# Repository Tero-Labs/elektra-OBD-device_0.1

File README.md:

> Designing Electric Vehicles capable of autonomously participating in a decentralized, sharing economy at a much lower cost than now.   

:warning: :warning: :warning:
>Deprecation Warning: 
This repo is no longer maintained. Please have a look at the newer [elektra-OBD-Device_v1.0](https://github.com/Tero-Labs/elektra-OBD-device_v1.0) based on the ESP32.

# Elektra-OBD-Device_v0.1
OBD data monitoring tool based on MCP2551 & MCP2515 for project elektra. The device is designed as a Raspberry Pi hat compatible with Raspberry Pi Zero W.

## Board 
Top             |  Bottom
:-------------------------:|:-------------------------:
  |  

Eagle project files  are given. The Cam output files are also present for ordering through PCB fabrication services.

## Assembly & Enclosure

Board             |  Enclosure
:-------------------------:|:-------------------------:
  |  

## Enclosure Printing Instructions
+ 0.3 layer height
+ PLA/ABS (ABS preferred)
+ 4x m1.5 countersink screws required

# License
<br />This work is licensed under a <a rel="license" href="http://creativecommons.org/licenses/by-nc-sa/4.0/">Creative Commons Attribution-NonCommercial-ShareAlike 4.0 International License</a>.

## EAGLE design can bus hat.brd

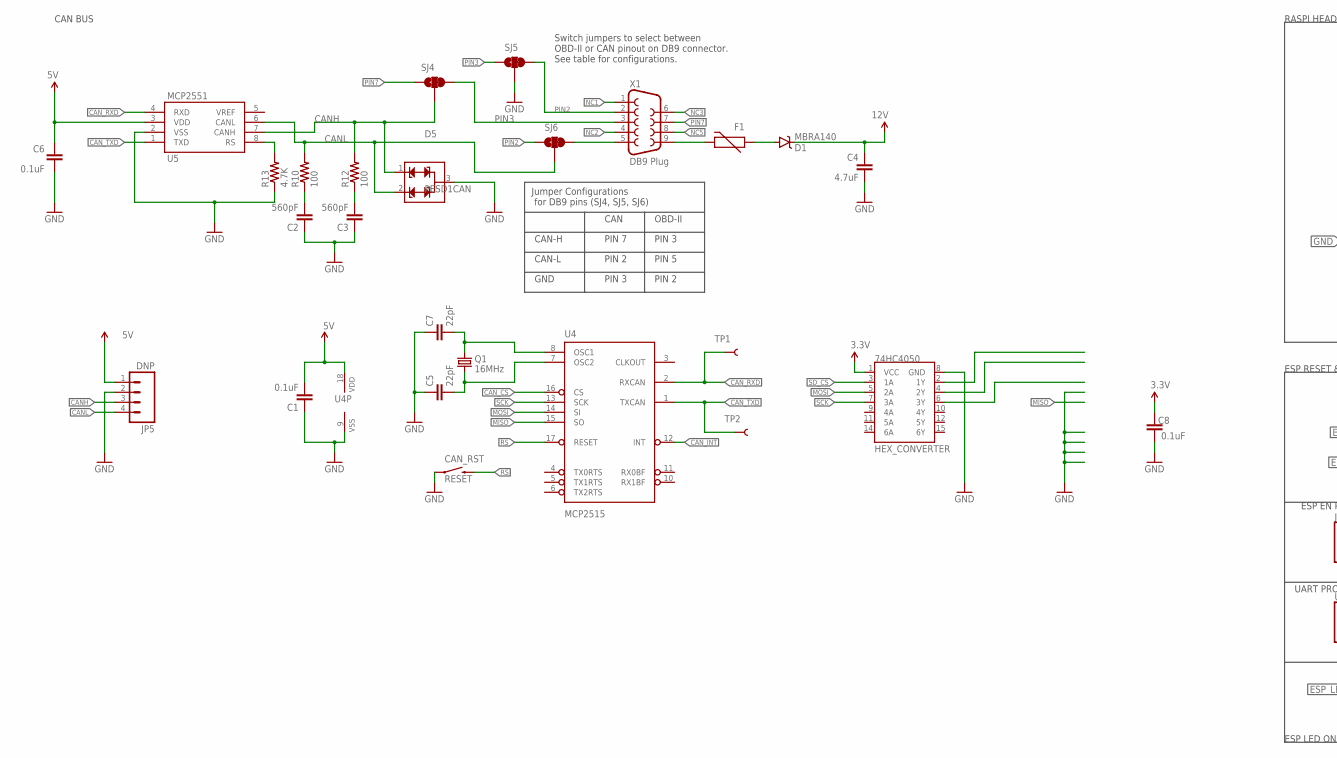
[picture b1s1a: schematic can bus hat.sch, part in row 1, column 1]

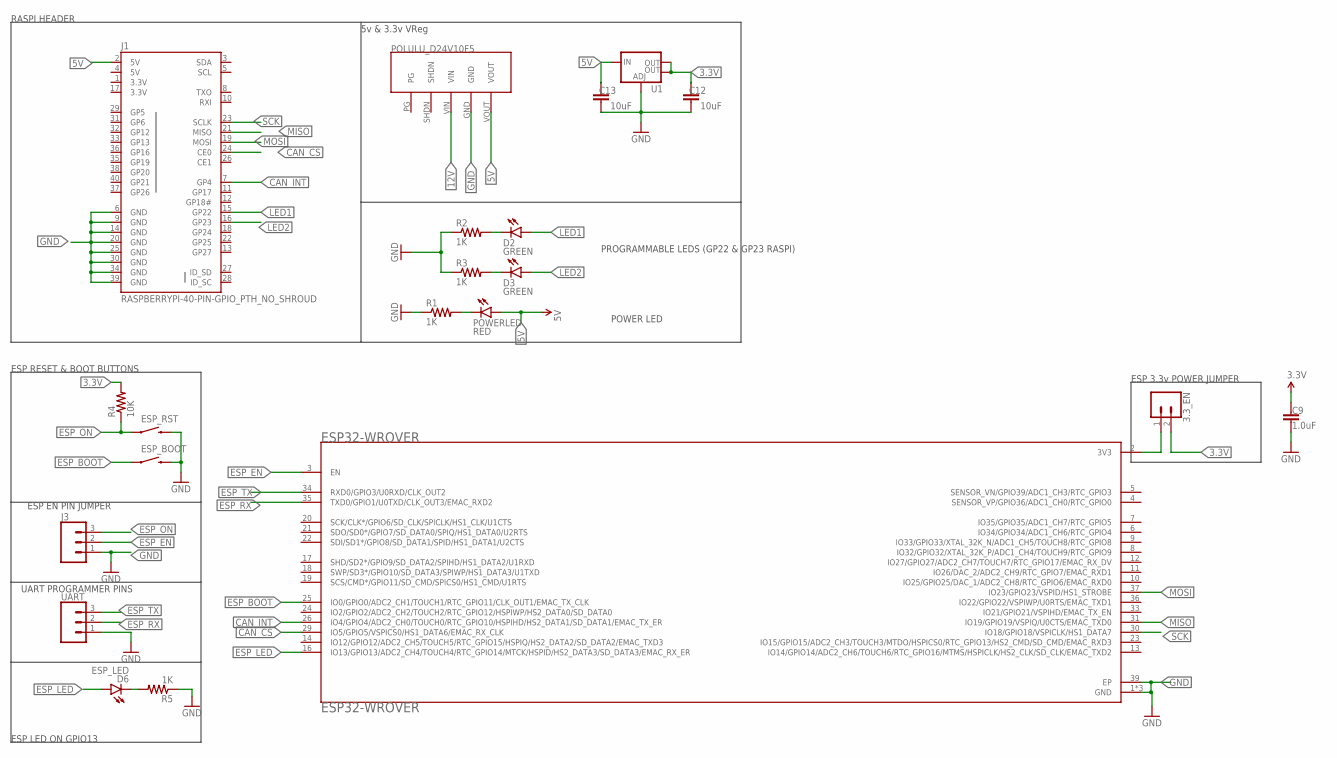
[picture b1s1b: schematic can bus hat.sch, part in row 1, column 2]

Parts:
3.3_EN: CONN_02; 1X02
74HC4050: HEX_CONVERTER; SO016
C1, C6, C8: 0.1uF; 0603-CAP
C2, C3: 560pF; 0603-CAP
C4: 4.7uF; 0603-CAP
C5, C7: 22pF; 0603-CAP
C9: 1.0uF; 0603-CAP
C12, C13: 10uF; 0603-CAP
CAN_RST: RESET; TACTILE-SWITCH-SMD
D1: MBRA140; SMA-DIODE
D2, D3: GREEN; LED-0603
D5: PESD1CAN; SOT23-3
D6: ESP_LED; LED-0603
ESP32-WROVER: ESP32-WROVER; XCVR_ESP32-WROVER
ESP_BOOT: RESET; TACTILE-SWITCH-SMD
ESP_RST: RESET; TACTILE-SWITCH-SMD
F1: PTCTHERMISTOR1206; PTC-1206
J1: RASPBERRYPI-40-PIN-GPIO_PTH_NO_SHROUD; 2X20
J3: CONN_03; 1X03
JP5: DNP; 1X04
POLULU_D24V10F5: POLOLU5V,1ASTEP-DOWNVOLTAGEREGULATORD24V10F5; POLULU-VREG
POWERLED: RED; LED-0603
Q1: 16MHz; CRYSTAL-SMD-5X3
R1, R2, R3, R5: 1K; 0603-RES
R4: 10K; 0603-RES
R10, R12: 100; 0603-RES
R13: 4.7K; 0603-RES
SJ4, SJ5, SJ6: JUMPER-PAD-3-2OF3_NC_BY_TRACE_SMALL; PAD-JUMPER-3-2OF3_NC_BY_TRACE_YES_SILK_FULL_BOX
TP1, TP2: TEST-POINT3X5; PAD.03X.05
U1: VR_REGULATOR_LM1117SOT223; SOT223
U4: MCP2515; SO-18W
U5: MCP2551; SO08
UART: CONN_03; 1X03
X1: DB9 Plug; DB9_MALE

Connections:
3.3V: 3.3_EN.2, 74HC4050.1 (VCC), C8.2, C9.1, C12.2, J1.1 (3.3V), J1.17 (3.3V), R4.2, U1.2 (OUT), U1.4 (OUT)
5V: C1.2, C6.2, C13.2, J1.2 (5V), J1.4 (5V), JP5.1, POLULU_D24V10F5.VOUT, POWERLED.A, U1.3 (IN), U4.18 (VDD), U5.3 (VDD)
12V: C4.1, D1.C, POLULU_D24V10F5.VIN
CANH: D5.1, JP5.3, R12.2, SJ4.2, U5.7 (CANH)
CANL: D5.2, JP5.4, R10.2, SJ6.2, U5.6 (CANL)
CAN_CS: ESP32-WROVER.29 (IO5/GPIO5/VSPICS0/HS1_DATA6/EMAC_RX_CLK), J1.24 (CE0), U4.16 (CS)
CAN_INT: ESP32-WROVER.26 (IO4/GPIO4/ADC2_CH0/TOUCH0/RTC_GPIO10/HS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), J1.7 (GP4), U4.12 (INT)
CAN_RXD: TP1.P$1, U4.2 (RXCAN), U5.4 (RXD)
CAN_TXD: TP2.P$1, U4.1 (TXCAN), U5.1 (TXD)
ESP_BOOT: ESP32-WROVER.25 (IO0/GPIO0/ADC2_CH1/TOUCH1/RTC_GPIO11/CL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), ESP_BOOT.1
ESP_EN: ESP32-WROVER.3 (EN), J3.2
ESP_LED: D6.A, ESP32-WROVER.16 (IO13/GPIO13/ADC2_CH4/TOUCH4/RTC_GPIO14/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)
ESP_ON: ESP_RST.1, J3.3, R4.1
ESP_RX: ESP32-WROVER.35 (TXD0/GPIO1/U0TXD/CLK_OUT3/EMAC_RXD2), UART.2
ESP_TX: ESP32-WROVER.34 (RXD0/GPIO3/U0RXD/CLK_OUT2), UART.3
GND: 74HC4050.8 (GND), C1.1, C2.1, C3.1, C4.2, C5.1, C6.1, C7.1, C8.1, C9.2, C12.1, C13.1, CAN_RST.1, D5.3, ESP32-WROVER.1 (GND), ESP32-WROVER.15 (GND), ESP32-WROVER.38 (GND), ESP32-WROVER.39 (EP), ESP_BOOT.3 (2), ESP_RST.3 (2), J1.6 (GND), J1.9 (GND), J1.14 (GND), J1.20 (GND), J1.25 (GND), J1.30 (GND), J1.34 (GND), J1.39 (GND), J3.1, JP5.2, POLULU_D24V10F5.GND, R1.1, R2.1, R3.1, R5.1, R13.1, SJ5.2, U1.1 (ADJ), U4.9 (VSS), U5.2 (VSS), UART.1
LED1: D2.A, J1.15 (GP22)
LED2: D3.A, J1.16 (GP23)
MISO: ESP32-WROVER.31 (IO19/GPIO19/VSPIQ/U0CTS/EMAC_TXD0), J1.21 (MISO), U4.15 (SO)
MOSI: 74HC4050.5 (2A), ESP32-WROVER.37 (IO23/GPIO23/VSPID/HS1_STROBE), J1.19 (MOSI), U4.14 (SI)
unnamed: SJ6.3, X1.5
unnamed: POWERLED.C, R1.2
unnamed: D2.C, R2.2
unnamed: D3.C, R3.2
unnamed: 3.3_EN.1, ESP32-WROVER.2 (3V3)
unnamed: C2.2, R10.1
unnamed: C3.2, R12.1
unnamed: D6.C, R5.2
unnamed: F1.2, X1.9
unnamed: R13.2, U5.8 (RS)
unnamed: D1.A, F1.1
unnamed: C7.2, Q1.3 (2), U4.8 (OSC1)
unnamed: C5.2, Q1.1, U4.7 (OSC2)
NC1: X1.1
NC2: X1.4
NC3: X1.6
NC5: X1.8
PIN2: SJ5.3, SJ6.1, X1.2
PIN3: SJ4.3, SJ5.1, X1.3
PIN7: SJ4.1, X1.7
RS: CAN_RST.3 (2), U4.17 (RESET)
SCK: 74HC4050.7 (3A), ESP32-WROVER.30 (IO18/GPIO18/VSPICLK/HS1_DATA7), J1.23 (SCLK), U4.13 (SCK)
SD_CS: 74HC4050.3 (1A)

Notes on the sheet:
CAN
OBD-II
CAN-H
CAN-L
GND
PIN 5
PIN 2
PIN 3
PIN 7
Jumper Configurations for DB9 pins (SJ4, SJ5, SJ6)
Switch jumpers to select between OBD-II or CAN pinout on DB9 connector. See table for configurations.
CAN BUS
5v & 3.3v VReg
RASPI HEADER
ESP RESET & BOOT BUTTONS
ESP EN PIN JUMPER
UART PROGRAMMER PINS
ESP LED ON GPIO13
ESP 3.3v POWER JUMPER
PROGRAMMABLE LEDS (GP22 & GP23 RASPI)
POWER LED

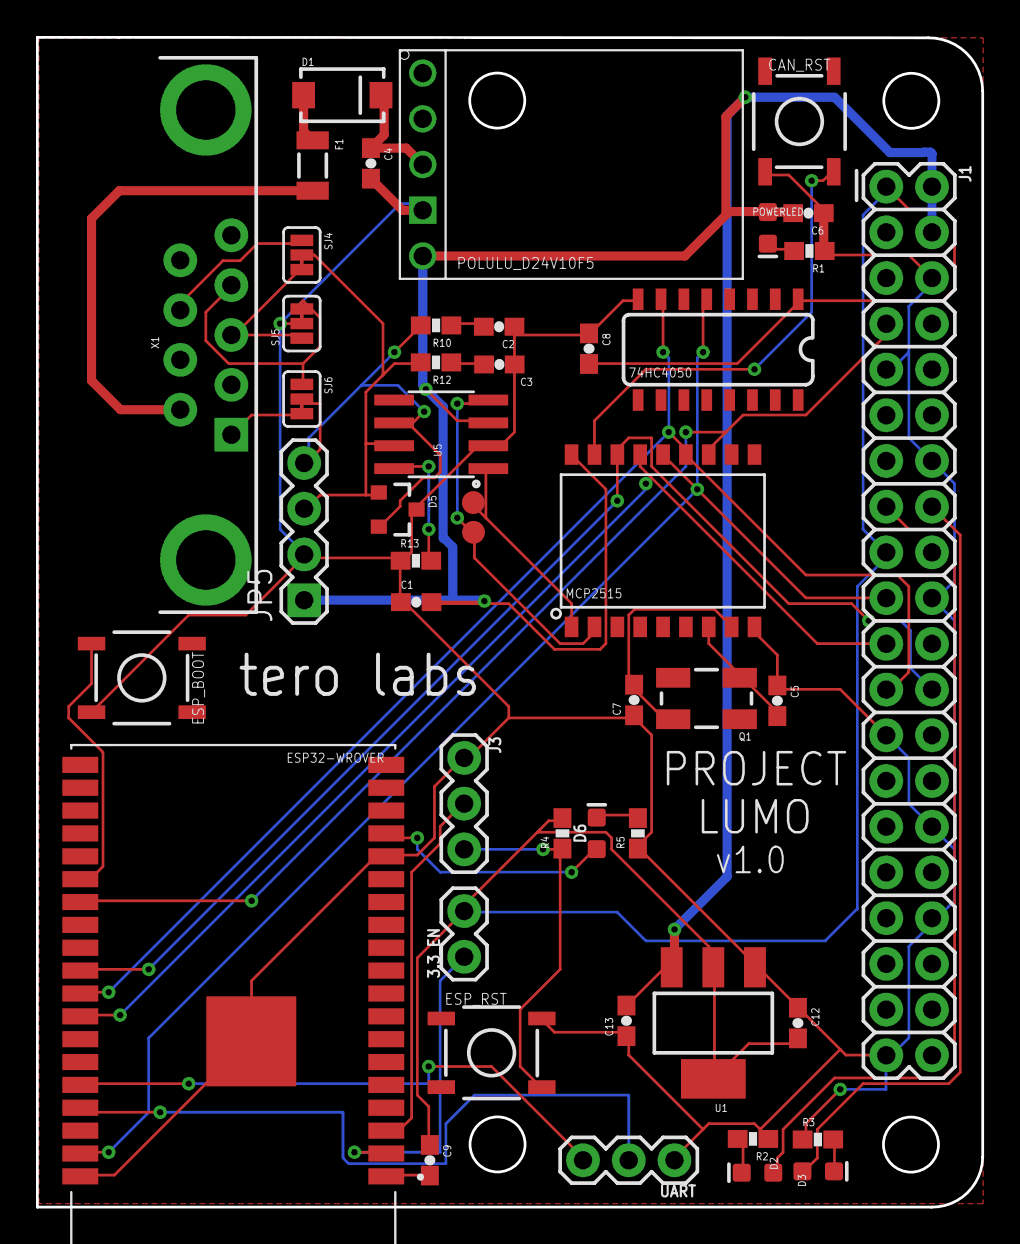
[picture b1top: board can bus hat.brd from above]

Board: 2 copper layers, 52.5 x 65.0 mm, 47 parts (0 on the bottom side), 38 nets.

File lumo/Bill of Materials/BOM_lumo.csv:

,Name,Value,Package,Quantity,Description,Link
Capacitors,"C5,C7,",22pF,"""0603""",2,,https://www.digikey.com/en/products/detail/vishay-vitramon/V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
,"C2,C3",560pF,"""0603""",2,,https://www.digikey.com/en/products/detail/vishay-vitramon/V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
,"C1,C6,C8",0.1uF,"""0603""",3,,https://www.digikey.com/en/products/detail/frontier-electron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
,C4,4.7uF,"""0603""",1,,OUT OF STOCK ON DIGIKEY
,"C12,C13",10uF,"""0603""",2,,https://www.digikey.com/en/products/detail/murata-electronic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
,,,,,,
Resistors,"R10,R12",100Ω,"""0603""",2,,
,"R1,R2,R3,",1kΩ,"""0603""",3,,
,R13,4.7kΩ,"""0603""",1,,
,"R4,R5",10k,"""0603""",2,,
,,,,,,
Diodes,D1,MBRA140,SMA-DIODE,1,,https://www.digikey.com/en/products/detail/on-semiconductor/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
,D5,PESD1CAN,SOT23-3,1,CAN bus ESD protection diode,https://www.digikey.com/en/products/detail/nexperia-usa-inc/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
,"D2,D3,D6,POWERLED",LED,"""0603""",4,,
,,,,,,
Fuse,F1,Resettable Fuse PTC,PTCTHERMISTOR1206,,,https://www.digikey.com/en/products/detail/littelfuse-inc/NA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
Crystal,Q1,16MHz,CRYSTAL-SMD-5X3,,,https://www.digikey.com/en/products/detail/cts-frequency-con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
,,,,,,
Connectors,,,,,,
,3.3_EN,1x02,Single Inline Male header,1,,https://www.digikey.com/en/products/detail/oupiin/2011H-1X40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
,"J3, UART",1x03,Single Inline Male header,2,,https://www.digikey.com/en/products/detail/oupiin/2011H-1X40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
,JP5,1x04,Single Inline Male header,1,,https://www.digikey.com/en/products/detail/oupiin/2011H-1X40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
,J1,2x20,Single Inline Female socket,1,,https://www.digikey.com/en/products/detail/adafruit-industri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
,X1,DB9 PLUG 90Degree PCB,DB9MALE,,,https://www.digikey.ch/product-detail/en/norcomp-inc/182-009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
,,,,,,
Buttons,"CAN)RST, ESP_BOOT, ESP_RST",SWITCH-MOMENTARY-2SMD,SWITCH-MOMENTARY-2SMD,,,https://www.digikey.com/en/products/detail/c-k/PTS526-SM15-S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
,,,,,,
Active Components,74HC4050,HEX_CONVERTER,SO016,1,,https://www.digikey.com/en/products/detail/texas-instruments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
,ESP32WROVER-B,ESP32,,1,,https://www.digikey.com/en/products/detail/espressif-systems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
,POLULU_D24V10F5,5v1A,,1,,https://www.pololu.com/product/2831
,LM1117SOT223,3.3v,SOT223,1,,https://www.digikey.com/en/products/detail/texas-instruments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
,MCP2515,,SO18w,1,,https://www.digikey.com/en/products/detail/microchip-technol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
,MCP2551,,SO08,1,,https://www.digikey.com/en/products/detail/microchip-technol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

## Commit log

2021-06-18 adding openxc firmware tools
2021-06-18 added vi-firmware
2021-07-13 Added lumo-can-bus-hat
2021-07-13 added new rendered assets
2021-07-13 adding readme
2021-07-13 updating readme
2021-07-13 vi-toolset added
2021-07-14 added license
2021-12-08 cleaning repo
2021-12-08 updated readme, fixed broken links

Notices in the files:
parts and their libraries:
SparkFun-Capacitors: Licensing: Creative Commons ShareAlike 4.0 International - https://creativecommons.org/licenses/by-sa/4.0
SparkFun-Connectors: Licensing: CC v3.0 Share-Alike You are welcome to use this library for commercial purposes.
